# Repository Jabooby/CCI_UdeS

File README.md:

# CCI_UdeS
Concours de Circuit Imprimé Université de Sherbrooke
## Compétition de Conception de PCB - Hacker Mouse

Bienvenue à la compétition de conception de PCB sur le thème "Hacker Mouse" ! Cette compétition vise à stimuler la créativité et l'innovation dans la conception de circuits imprimés pour créer une souris d'ordinateur unique et fonctionnelle.

### Compétition

#### Répertoire "Competition"
Le répertoire "Competition" contient tous les documents nécessaires pour participer à la compétition Hacker Mouse. Vous y trouverez :
- Les règles de la compétition
- Les critères de notation
- Les dates importantes
- Les détails sur les inscriptions
- Autres ressources utiles

#### Répertoires des Équipes
Chaque équipe participant à la compétition aura son propre répertoire dédié dans lequel elle pourra stocker ses fichiers de conception, ses notes, ses schémas, ses designs de PCB et toute autre documentation pertinente liée à son projet.

### Documentation

#### Répertoire "Documentation"
Le répertoire "Documentation" contient des fichiers PDF de datasheets des microcontrôleurs acceptés pour la compétition. Ces documents sont essentiels pour comprendre les spécifications techniques des composants utilisés dans la conception des "Hacker Mouse".

### Ressources Supplémentaires

- Si vous avez des questions ou avez besoin d'aide, n'hésitez pas à nous contacter.
- Rejoignez notre canal Discord pour discuter avec d'autres participants et obtenir des conseils et des astuces.

Nous vous souhaitons bonne chance et avons hâte de voir vos créations !

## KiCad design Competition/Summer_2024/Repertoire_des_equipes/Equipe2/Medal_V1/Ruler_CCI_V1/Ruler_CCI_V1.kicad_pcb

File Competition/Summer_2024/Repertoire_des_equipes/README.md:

# Création de "Branch"

 1. Cliquez sur le rectangle avec le logo de "Branche". 
 2. Puis cliquez sur "View all branches".

 3. Dans la nouvelle fenêtre, cliquez sur "New branch".

 4. Choisissez un nom de "Branch" et appuyez sur "Create new branch".

 5. Votre "Branch" est maitenant créé. Vous pouvez ouvrir "GitHub Desktop" ou "GitKraken" et sélectionner la "Branch" que vous voulez.

 6. Bon codage!

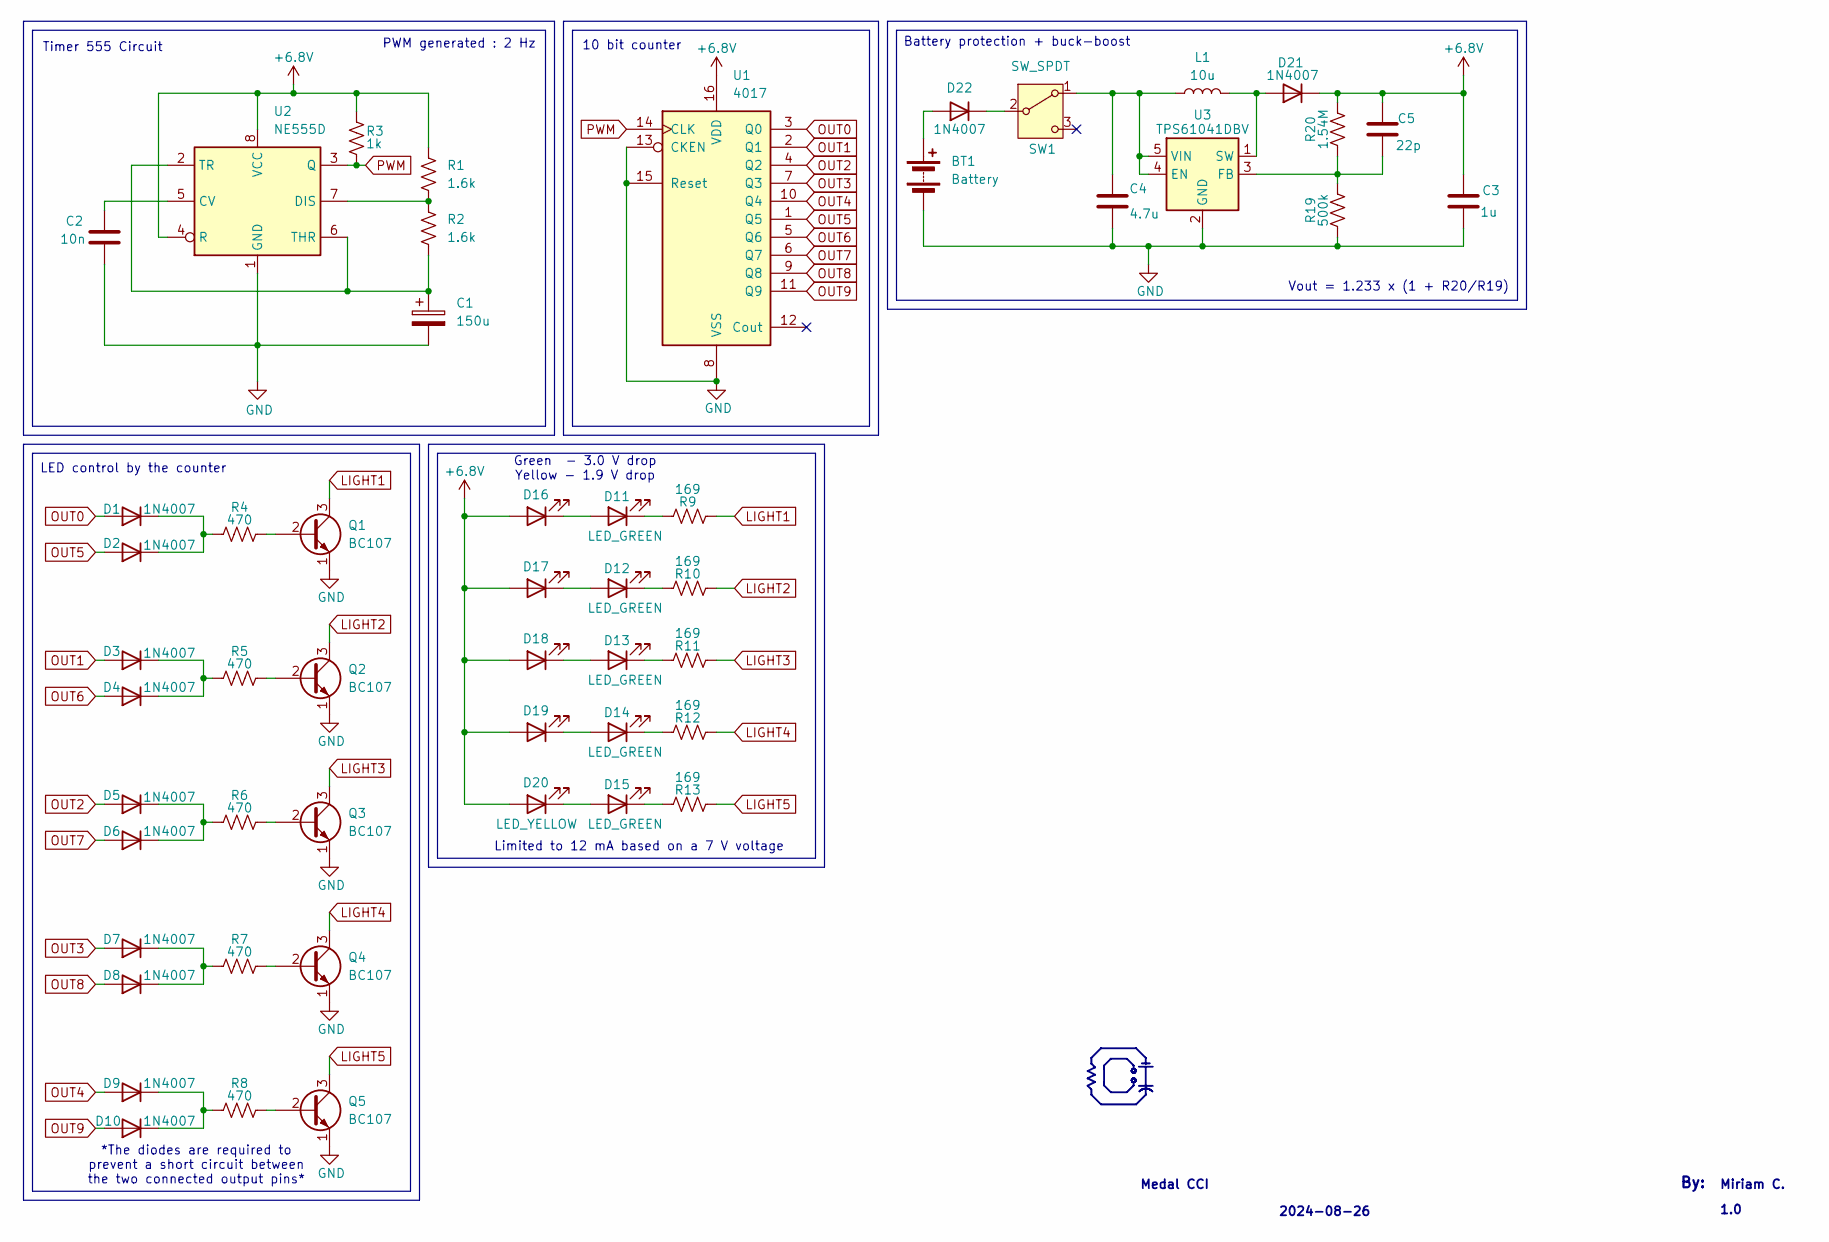
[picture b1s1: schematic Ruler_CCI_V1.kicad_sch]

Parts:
BT1: Battery; BAT_SMD_CR1220
C1: 150u; CP_Elec_6.3x7.7
C2: 10n; C_0603_1608Metric
C3: 1u; L_0603_1608Metric_Pad1.05x0.95mm_HandSolder
C4: 4.7u; L_0603_1608Metric_Pad1.05x0.95mm_HandSolder
C5: 22p; L_0603_1608Metric_Pad1.05x0.95mm_HandSolder
D1, D2, D3, D4, D5, D6, D7, D8, D9, D10, D21, D22: 1N4007; D_SOD-123F
D11, D12, D13, D14, D15: LED_GREEN; D_0603_1608Metric_Pad1.05x0.95mm_HandSolder
D16, D17, D18, D19, D20: LED_YELLOW; D_0603_1608Metric_Pad1.05x0.95mm_HandSolder
L1: 10u; L_0805_2012Metric_Pad1.15x1.40mm_HandSolder
Q1, Q2, Q3, Q4, Q5: BC107; SOT-23
R1, R2: 1.6k; R_0603_1608Metric_Pad0.98x0.95mm_HandSolder
R3: 1k; R_0603_1608Metric_Pad0.98x0.95mm_HandSolder
R4, R5, R6, R7, R8: 470; R_0603_1608Metric_Pad0.98x0.95mm_HandSolder
R9, R10, R11, R12, R13: 169; R_0603_1608Metric_Pad0.98x0.95mm_HandSolder
R19: 500k; R_0603_1608Metric_Pad0.98x0.95mm_HandSolder
R20: 1.54M; R_0603_1608Metric_Pad0.98x0.95mm_HandSolder
SW1: SW_SPDT; SW_SPDT_PCM12
U1: 4017; SOP-16_3.9x9.9mm_P1.27mm
U2: NE555D; SOIC-8_3.9x4.9mm_P1.27mm
U3: TPS61041DBV; SOT-23-5

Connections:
+6.8V: C3.1, C5.1, D16.2 (A), D17.2 (A), D18.2 (A), D19.2 (A), D20.2 (A), D21.1 (K), R1.1, R3.1, R20.2, U1.16 (VDD), U2.4 (R), U2.8 (VCC)
GND: BT1.2 (-), C1.2, C2.2, C3.2, C4.2, Q1.1 (E), Q2.1 (E), Q3.1 (E), Q4.1 (E), Q5.1 (E), R19.1, U1.8 (VSS), U1.13 (CKEN), U1.15 (Reset), U2.1 (GND), U3.2 (GND)
LIGHT1: Q1.3 (C), R9.1
LIGHT2: Q2.3 (C), R10.1
LIGHT3: Q3.3 (C), R11.1
LIGHT4: Q4.3 (C), R12.1
LIGHT5: Q5.3 (C), R13.1
unnamed: BT1.1 (+), D22.2 (A)
unnamed: D1.1 (K), D2.1 (K), R4.1
unnamed: D3.1 (K), D4.1 (K), R5.1
unnamed: D5.1 (K), D6.1 (K), R6.1
unnamed: D7.1 (K), D8.1 (K), R7.1
unnamed: D9.1 (K), D10.1 (K), R8.1
unnamed: D11.2 (A), D16.1 (K)
unnamed: D11.1 (K), R9.2
unnamed: D12.2 (A), D17.1 (K)
unnamed: D12.1 (K), R10.2
unnamed: D13.2 (A), D18.1 (K)
unnamed: D13.1 (K), R11.2
unnamed: D14.2 (A), D19.1 (K)
unnamed: D14.1 (K), R12.2
unnamed: D15.2 (A), D20.1 (K)
unnamed: D15.1 (K), R13.2
unnamed: D21.2 (A), L1.2, U3.1 (SW)
unnamed: D22.1 (K), SW1.2 (B)
unnamed: Q1.2 (B), R4.2
unnamed: Q2.2 (B), R5.2
unnamed: Q3.2 (B), R6.2
unnamed: Q4.2 (B), R7.2
unnamed: Q5.2 (B), R8.2
unnamed: C4.1, L1.1, SW1.1 (A), U3.4 (EN), U3.5 (VIN)
unnamed: C2.1, U2.5 (CV)
unnamed: R1.2, R2.1, U2.7 (DIS)
unnamed: C1.1, R2.2, U2.2 (TR), U2.6 (THR)
unnamed: C5.2, R19.2, R20.1, U3.3 (FB)
OUT0: D1.2 (A), U1.3 (Q0)
OUT1: D3.2 (A), U1.2 (Q1)
OUT2: D5.2 (A), U1.4 (Q2)
OUT3: D7.2 (A), U1.7 (Q3)
OUT4: D9.2 (A), U1.10 (Q4)
OUT5: D2.2 (A), U1.1 (Q5)
OUT6: D4.2 (A), U1.5 (Q6)
OUT7: D6.2 (A), U1.6 (Q7)
OUT8: D8.2 (A), U1.9 (Q8)
OUT9: D10.2 (A), U1.11 (Q9)
PWM: R3.2, U1.14 (CLK), U2.3 (Q)

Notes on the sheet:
Miriam C.
10 bit counter
2024-08-26
Limited to 12 mA based on a 7 V voltage
LED control by the counter
Green - 3.0 V drop Yellow - 1.9 V drop
By:
1.0
Battery protection + buck-boost
PWM generated : 2 Hz
Timer 555 Circuit
*The diodes are required to prevent a short circuit between the two connected output pins*
Vout = 1.233 x (1 + R20/R19)
Medal CCI

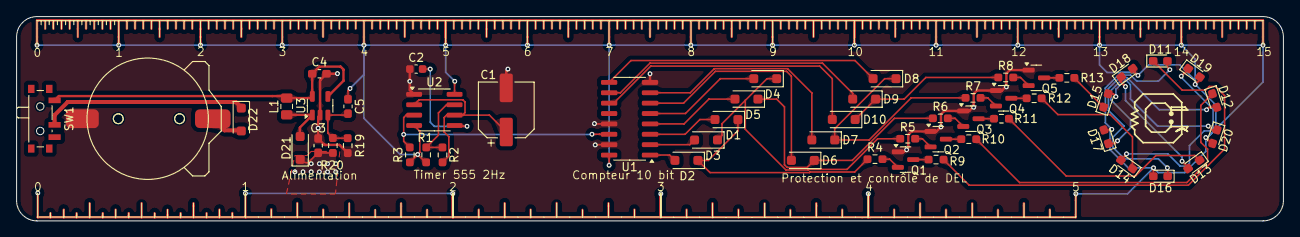
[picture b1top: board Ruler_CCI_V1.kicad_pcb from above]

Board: 2 copper layers, 155.0 x 25.0 mm, 53 parts (0 on the bottom side), 46 nets.

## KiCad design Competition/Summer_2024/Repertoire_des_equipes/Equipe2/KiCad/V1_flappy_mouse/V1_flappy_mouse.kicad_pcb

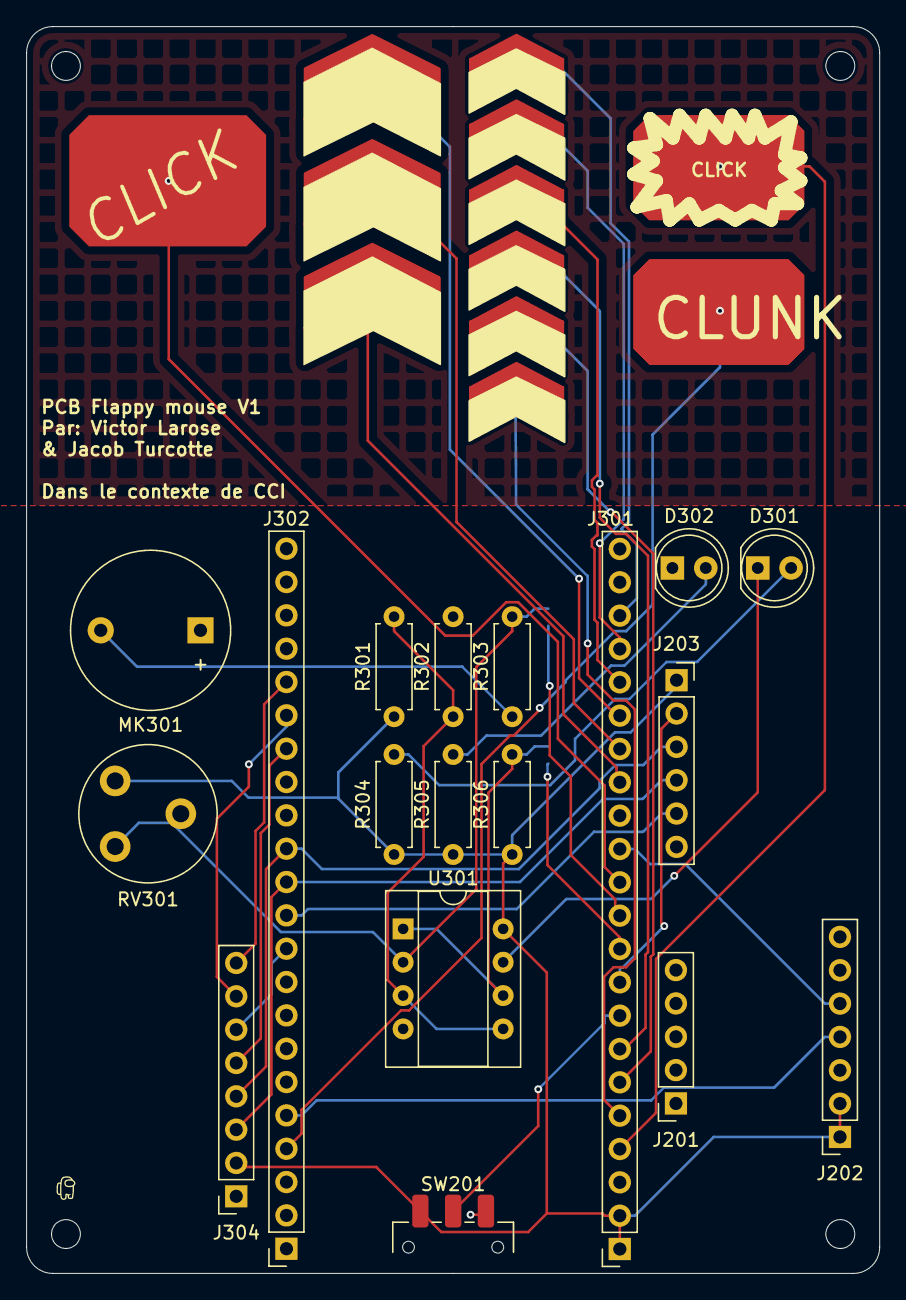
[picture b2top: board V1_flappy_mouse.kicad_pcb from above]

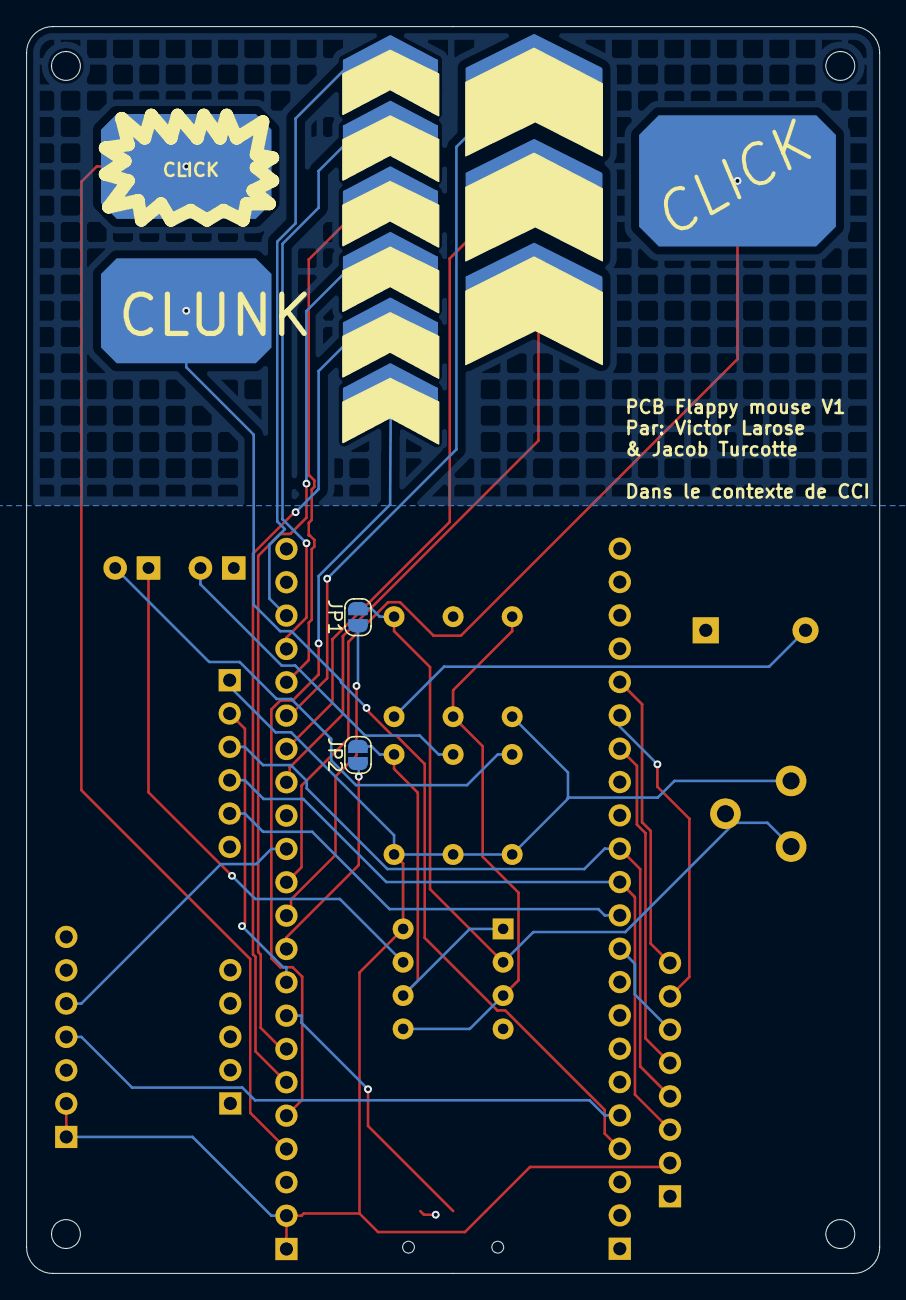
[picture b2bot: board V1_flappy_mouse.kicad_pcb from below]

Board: 4 copper layers, 65.0 x 95.0 mm, 43 parts (14 on the bottom side), 34 nets.

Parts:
D301: TRIG LED; LED_D5.0mm_IRGrey
D302: PWR LED; LED_D5.0mm_IRGrey
J201: Conn_01x05_no_connect(SPI); PinSocket_1x05_P2.54mm_Vertical
J202: Conn_accelerometer_I2C; PinSocket_1x07_P2.54mm_Vertical
J203: Conn_Module_SD; PinSocket_1x06_P2.54mm_Vertical
J301: ESP_GAUCHE; PinSocket_1x22_P2.54mm_Vertical
J302: ESP_DROIT; PinSocket_1x22_P2.54mm_Vertical
J304: Conn_TFT_display; PinSocket_1x08_P2.54mm_Vertical
JP1: SolderJumper_AOUT; SolderJumper-2_P1.3mm_Open_RoundedPad1.0x1.5mm
JP2: SolderJumper_DOUT; SolderJumper-2_P1.3mm_Open_RoundedPad1.0x1.5mm
MK301: Mic; Buzzer_12x9.5RM7.6
R301, R302: 100K; R_Axial_DIN0207_L6.3mm_D2.5mm_P7.62mm_Horizontal
R303: 150; R_Axial_DIN0207_L6.3mm_D2.5mm_P7.62mm_Horizontal
R304, R305: 1K; R_Axial_DIN0207_L6.3mm_D2.5mm_P7.62mm_Horizontal
R306: 10K; R_Axial_DIN0207_L6.3mm_D2.5mm_P7.62mm_Horizontal
RV301: 10K; Potentiometer_Piher_PT-10-V05_Vertical
SW201: JS102011JAQN; SW_SPDT_CK_JS102011SAQN
TP5, TP5#2: Touchpad_click_gauche; Touchpad_biz_rect_smaller
TP6, TP6#2: Touchpad_scroll4; Touchpad_slider_smaller
TP7, TP7#2: Touchpad_scroll5; Touchpad_slider_smaller
TP8, TP8#2: Touchpad_scroll6; Touchpad_slider_smaller
TP9, TP9#2: Touchpad_scroll7; Touchpad_slider_smaller
TP10, TP10#2: Touchpad_scroll8; Touchpad_slider_smaller
TP11, TP11#2: Touchpad_scroll9; Touchpad_slider_smaller
TP12, TP12#2: Touchpad_stopMouseMotion; Touchpad_biz_rect_smaller
TP201: Touchpad_click_droit; Touchpad_biz_rect
TP202, TP202#2: Touchpad_scroll1; Touchpad_slider
TP203, TP203#2: Touchpad_scroll2; Touchpad_slider
TP204, TP204#2: Touchpad_scroll3; Touchpad_slider
U301: LM393; CERDIP-8_W7.62mm_SideBrazed_Socket

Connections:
+3.3V: J202.1, J202.2, J203.1, J301.1, J301.2, J304.2, R301.1, R304.1, R305.1, R306.1, RV301.3, SW201.1 (A), U301.8 (V+)
FSPICLK/TOUCH12/GPIO12: J301.18, TP9.1, TP9#2.1
FSPICS0/TOUCH10/GPIO10: J301.16, TP203.1, TP203#2.1
FSPID/TOUCH11/GPIO11: J301.17, TP204.1, TP204#2.1
FSPIHD/TOUCH9/GPIO9: J301.15, TP202.1, TP202#2.1
FSPIQ/TOUCH13/GPIO13: J301.19, TP10.1, TP10#2.1
FSPIWP/TOUCH14/GPIO14: J301.20, TP11.1, TP11#2.1
GND: D302.1 (K), J202.3, J202.7, J203.6, J301.22, J302.1, J302.21, J302.22, J304.1, MK301.1 (-), R302.2, SW201.3 (C), U301.4 (V-)
GPIO1/TOUCH1/ADC1_0/SDA0: J302.4, TP12.1, TP12#2.1
GPIO2/TOUCH2/ADC1_1/SCL1: J202.4, J302.5
GPIO21: J302.18, J304.8
GPIO35/FSPID: J203.3, J302.13, J304.4
GPIO36/FSPICLK: J203.4, J302.12, J304.3
GPIO37/FSPIQ: J203.5, J302.11
GPIO38/FSPIWP/RGB_LED: J302.10, J304.6
GPIO47/SPICLK_P: J302.17, J304.7
GPIO48/SPICLK_N: J302.16, J304.5
JTAG/TOUCH3/SDA1/GPIO3: J202.5, J301.13
unnamed: D301.2 (A), R304.2
unnamed: D301.1 (K), U301.7
unnamed: D302.2 (A), R305.2
unnamed: JP1.1 (A), R303.2, RV301.1, RV301.2, U301.2 (-)
unnamed: JP2.1 (A), R306.2, U301.1, U301.6 (-)
unnamed: MK301.2 (+), R303.1
unnamed: R301.2, R302.1, U301.3 (+), U301.5 (+)
TOUCH4/GPIO4: J301.4, TP5.1, TP5#2.1
TOUCH5/GPIO5: J301.5, TP6.1, TP6#2.1
TOUCH6/GPIO6: J301.6, TP7.1, TP7#2.1
TOUCH7/GPIO7: J301.7, TP8.1, TP8#2.1
TOUCH8/GPIO8: J301.12, TP201.1
U0CTS/GPIO16: J203.2, J301.9
U0RTS/GPIO15: J301.8, SW201.2 (B)
U1RXD/GPIO18: J301.11, JP1.2 (B)
U1TXD/GPIO17: J301.10, JP2.2 (B)

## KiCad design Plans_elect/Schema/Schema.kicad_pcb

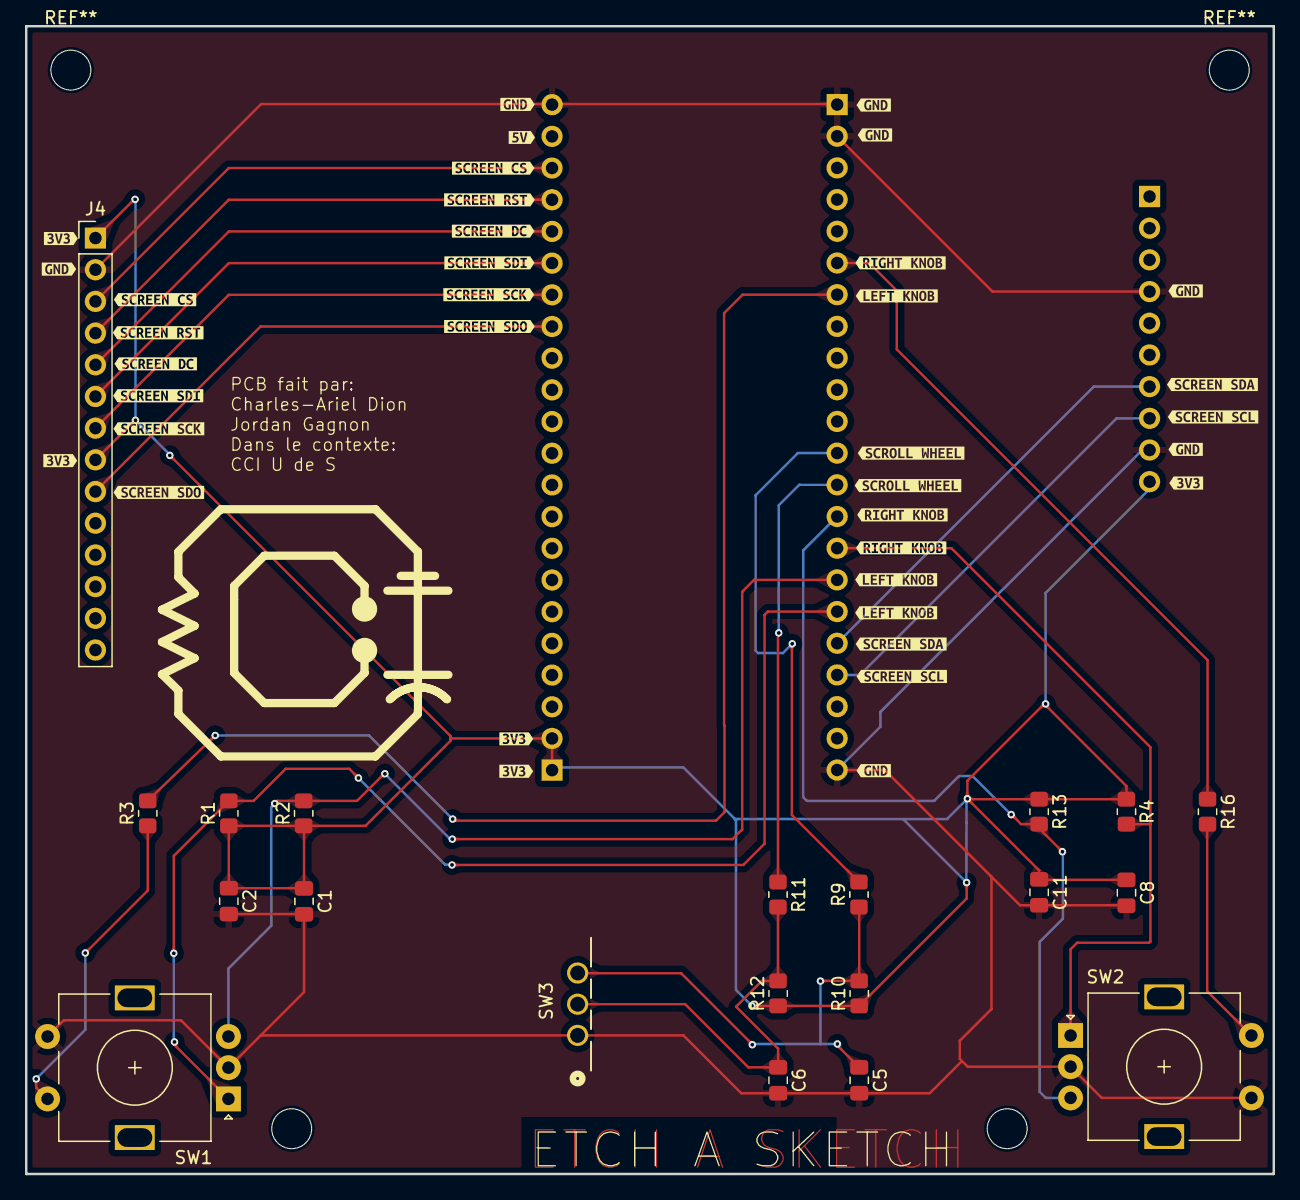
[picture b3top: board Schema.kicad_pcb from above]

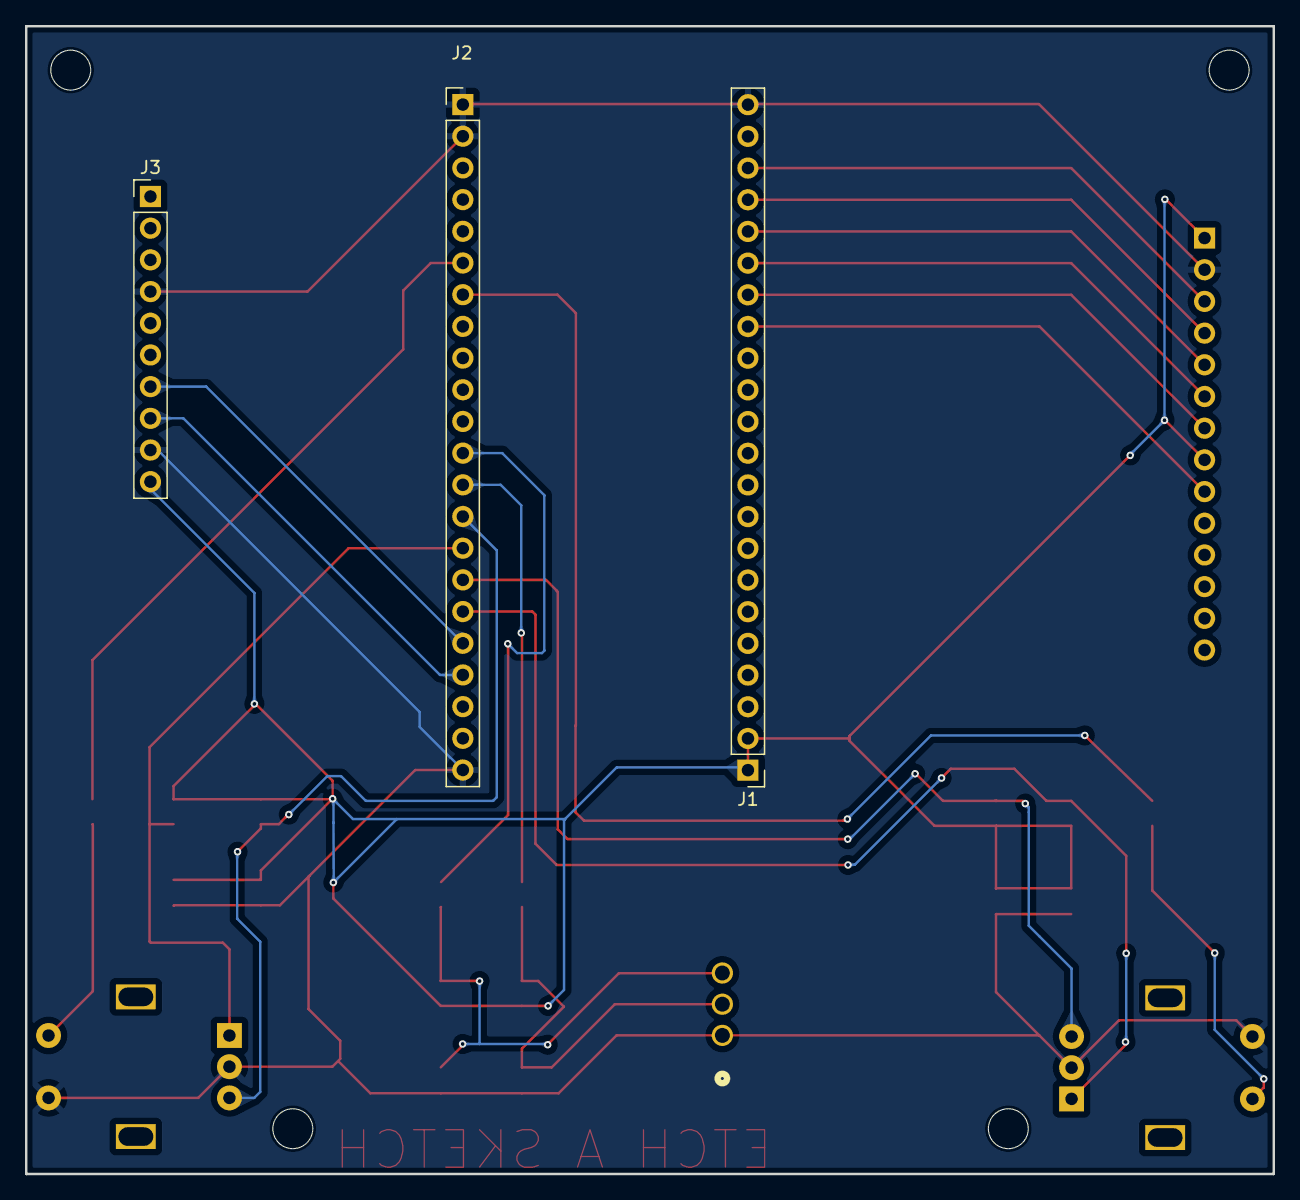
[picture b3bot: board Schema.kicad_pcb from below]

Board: 2 copper layers, 100.0 x 92.0 mm, 60 parts (3 on the bottom side), 22 nets.

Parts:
C1, C2, C8, C11: 100nF; C_0805_2012Metric_Pad1.18x1.45mm_HandSolder
C5, C6: 22nF; C_0805_2012Metric_Pad1.18x1.45mm_HandSolder
J1, J2: Conn_01x22; PinHeader_1x22_P2.54mm_Vertical
J3: Conn_01x10; PinHeader_1x10_P2.54mm_Vertical
J4: Conn_01x14; PinHeader_1x14_P2.54mm_Vertical
R1, R2, R3, R4, R13, R16: 1K; R_0805_2012Metric_Pad1.20x1.40mm_HandSolder
R9, R10, R11, R12: 10K; R_0805_2012Metric_Pad1.20x1.40mm_HandSolder
SW1, SW2: RotaryEncoder_Switch; RotaryEncoder_Alps_EC11E-Switch_Vertical_H20mm
SW3: RotaryEncoder; EN10HT_BIT
kibuzzard-66ACC1A1: G***; kibuzzard-66ACC1A1
kibuzzard-66ACC1C4: G***; kibuzzard-66ACC1C4
kibuzzard-66ACC1D0: G***; kibuzzard-66ACC1D0
kibuzzard-66ACC1F2: G***; kibuzzard-66ACC1F2
kibuzzard-66ACC2A7, kibuzzard-66ACC2A7#2, kibuzzard-66ACC2A7#3: G***; kibuzzard-66ACC2A7
kibuzzard-66ACC2DC, kibuzzard-66ACC2DC#2, kibuzzard-66ACC2DC#3: G***; kibuzzard-66ACC2DC
kibuzzard-66ACC3A5, kibuzzard-66ACC3A5#2: G***; kibuzzard-66ACC3A5
kibuzzard-66ACC4A4: G***; kibuzzard-66ACC4A4
kibuzzard-66ACC4E0: G***; kibuzzard-66ACC4E0
kibuzzard-66ACC21E: G***; kibuzzard-66ACC21E
kibuzzard-66ACC22A: G***; kibuzzard-66ACC22A
kibuzzard-66ACC25D, kibuzzard-66ACC25D#2, kibuzzard-66ACC25D#3, kibuzzard-66ACC25D#4: G***; kibuzzard-66ACC25D
kibuzzard-66ACC45C: G***; kibuzzard-66ACC45C
kibuzzard-66ACC46C: G***; kibuzzard-66ACC46C
kibuzzard-66ACC47C: G***; kibuzzard-66ACC47C
kibuzzard-66ACC49B: G***; kibuzzard-66ACC49B
kibuzzard-66ACC153, kibuzzard-66ACC153#2: G***; kibuzzard-66ACC153
kibuzzard-66ACC180, kibuzzard-66ACC180#2, kibuzzard-66ACC180#3, kibuzzard-66ACC180#4: G***; kibuzzard-66ACC180
kibuzzard-66ACC204: G***; kibuzzard-66ACC204
kibuzzard-66ACC281: G***; kibuzzard-66ACC281
kibuzzard-66ACC309, kibuzzard-66ACC309#2: G***; kibuzzard-66ACC309
kibuzzard-66ACC392, kibuzzard-66ACC392#2: G***; kibuzzard-66ACC392
kibuzzard-66ACC438: G***; kibuzzard-66ACC438

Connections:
3V3: C1.1, C2.1, C8.1, C11.1, J1.1, J1.2, J3.10, J4.1, J4.8, R1.1, R2.1, R4.1, R10.1, R12.1, R13.1
/GPIO1-SCL: J2.19, J3.8
/GPIO2-SDA: J2.18, J3.7
/GPIO9-SDO: J1.15, J4.9
/GPIO10-SCk: J1.16, J4.7
/GPIO11-SDI: J1.17, J4.6
/GPIO12-DC: J1.18, J4.5
/GPIO13-RESET: J1.19, J4.4
/GPIO14-CS: J1.20, J4.3
/GPIO37-chB_S: J2.12, R9.2
/GPIO38_chA_S: J2.13, R11.1
/GPIO39-chB_Y: J2.14, R13.2, SW2.B
/GPIO40-chA_Y: J2.15, R4.2, SW2.A
/GPIO41-chB_X: J2.16, R2.2, SW1.B
/GPIO42-chA_X: J2.17, R1.2, SW1.A
/GPIO47-BSW2: J2.6, R16.1
/GPIO48-BSW1: J2.7, R3.2
GND: C1.2, C2.2, C5.2, C6.2, C8.2, C11.2, J1.22, J2.1, J2.2, J2.22, J3.4, J3.9, J4.2, SW1.C, SW1.S1, SW2.C, SW2.S1
unnamed: C5.1, R9.1, R10.2
unnamed: C6.1, R11.2, R12.2
unnamed: R3.1, SW1.S2
unnamed: R16.2, SW2.S2

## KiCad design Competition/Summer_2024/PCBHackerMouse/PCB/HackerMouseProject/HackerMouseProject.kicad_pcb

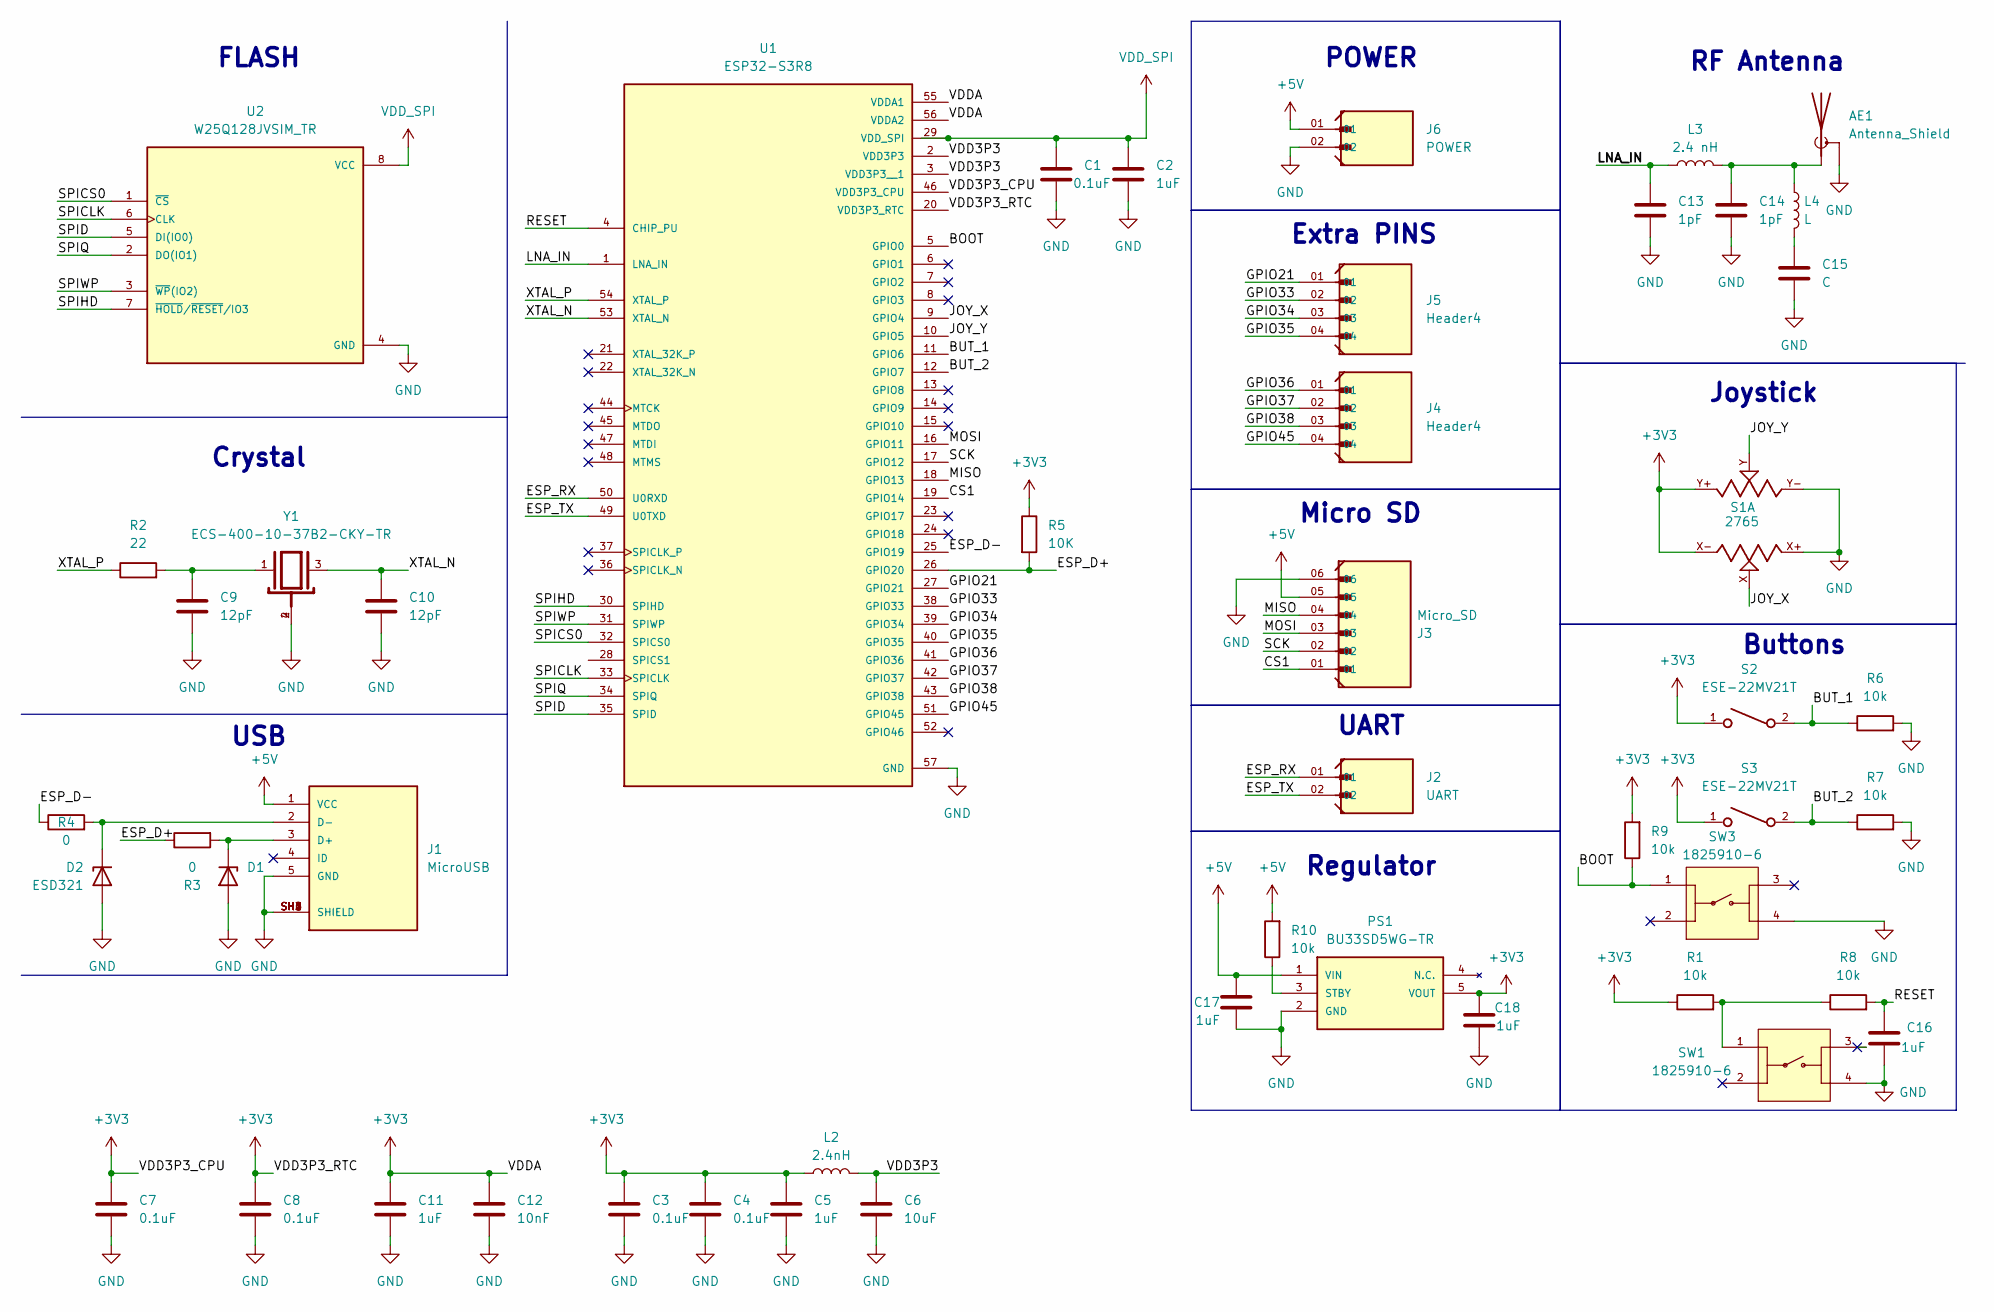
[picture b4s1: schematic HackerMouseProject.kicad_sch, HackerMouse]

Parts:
AE1: Antenna_Shield
C1, C3, C4, C7, C8: 0.1uF; C_0603_1608Metric_Pad1.08x0.95mm_HandSolder
C2, C5, C11, C16, C17, C18: 1uF; C_0603_1608Metric_Pad1.08x0.95mm_HandSolder
C6: 10uF; C_0603_1608Metric_Pad1.08x0.95mm_HandSolder
C9, C10: 12pF; C_0603_1608Metric_Pad1.08x0.95mm_HandSolder
C12: 10nF; C_0603_1608Metric_Pad1.08x0.95mm_HandSolder
C13, C14: 1pF; C_0603_1608Metric_Pad1.08x0.95mm_HandSolder
C15: C; C_0603_1608Metric_Pad1.08x0.95mm_HandSolder
D1, D2: ESD321; D_SOD-523
J1: MicroUSB; AMPHENOL_10118194-0001LF; PARTREV D
J2: UART; WURTH_61300211121; PARTREV 07/31/2015
J3: Micro_SD; WURTH_61300611121
J4, J5: Header4; WURTH_61300411121
J6: POWER; WURTH_61300211121; PARTREV 07/31/2015
L2: 2.4nH; C_0603_1608Metric_Pad1.08x0.95mm_HandSolder
L3: 2.4 nH; C_0603_1608Metric_Pad1.08x0.95mm_HandSolder
L4: L; C_0603_1608Metric_Pad1.08x0.95mm_HandSolder
PS1: BU33SD5WG-TR; SOT95P280X125-5N; MOUSER_PART_NUMBER 755-BU33SD5WG-TR
R1, R6, R7, R8, R9, R10: 10k; R_0603_1608Metric_Pad0.98x0.95mm_HandSolder
R2: 22; R_0603_1608Metric_Pad0.98x0.95mm_HandSolder
R3, R4: 0; R_0603_1608Metric_Pad0.98x0.95mm_HandSolder
R5: 10K; R_0603_1608Metric_Pad0.98x0.95mm_HandSolder
S1: 2765
S2, S3: ESE-22MV21T; SW_ESE-22MV21T
SW1, SW3: 1825910-6; SW_1825910-6-4; PARTREV C10
U1: ESP32-S3R8; QFN40P700X700X90-57N
U2: W25Q128JVSIM_TR; PARTREV C
Y1: ECS-400-10-37B2-CKY-TR; XTAL_ECS-400-10-37B2-CKY-TR; PARTREV Rev.2021

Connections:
+3V3: C3.1, C4.1, C5.1, C7.1, C8.1, C11.1, C12.1, C18.1, L2.2, PS1.5 (VOUT), R1.1, R5.1, R9.2, S1.X-, S1.Y+, S2.1, S3.1, U1.20 (VDD3P3_RTC), U1.46 (VDD3P3_CPU), U1.55 (VDDA1), U1.56 (VDDA2)
+5V: C17.1, J1.1 (VCC), J3.05, J6.01, PS1.1 (VIN), R10.2
/BOOT: R9.1, SW3.1, U1.5 (GPIO0)
/BUT_1: R6.1, S2.2, U1.11 (GPIO6)
/BUT_2: R7.1, S3.2, U1.12 (GPIO7)
/CS1: J3.01, U1.19 (GPIO14)
/ESP_D+: R3.1, R5.2, U1.26 (GPIO20)
/ESP_D-: R4.1, U1.25 (GPIO19)
/ESP_RX: J2.01, U1.50 (U0RXD)
/ESP_TX: J2.02, U1.49 (U0TXD)
/GPIO21: J5.01, U1.27 (GPIO21)
/GPIO33: J5.02, U1.38 (GPIO33)
/GPIO34: J5.03, U1.39 (GPIO34)
/GPIO35: J5.04, U1.40 (GPIO35)
/GPIO36: J4.01, U1.41 (GPIO36)
/GPIO37: J4.02, U1.42 (GPIO37)
/GPIO38: J4.03, U1.43 (GPIO38)
/GPIO45: J4.04, U1.51 (GPIO45)
/JOY_X: S1.X, U1.9 (GPIO4)
/JOY_Y: S1.Y, U1.10 (GPIO5)
/LNA_IN: C13.1, L3.1, U1.1 (LNA_IN)
/MISO: J3.04, U1.18 (GPIO13)
/MOSI: J3.03, U1.16 (GPIO11)
/RESET: C16.1, R8.2, U1.4 (CHIP_PU)
/SCK: J3.02, U1.17 (GPIO12)
/SPICLK: U1.33 (SPICLK), U2.6 (CLK)
/SPICS0: U1.32 (SPICS0), U2.1 (~CS)
/SPID: U1.35 (SPID), U2.5 (DI(IO0))
/SPIHD: U1.30 (SPIHD), U2.7 (~HOLD/~RESET/IO3)
/SPIQ: U1.34 (SPIQ), U2.2 (DO(IO1))
/SPIWP: U1.31 (SPIWP), U2.3 (~WP(IO2))
/VDD3P3: C6.1, L2.1, U1.2 (VDD3P3), U1.3 (VDD3P3__1)
/XTAL_N: C10.1, U1.53 (XTAL_N), Y1.3
/XTAL_P: R2.1, U1.54 (XTAL_P)
GND: AE1.2 (Shield), C1.2, C2.2, C3.2, C4.2, C5.2, C6.2, C7.2, C8.2, C9.2, C10.2, C11.2, C12.2, C13.2, C14.2, C15.2, C16.2, C17.2, C18.2, D1.2 (A), D2.2 (A), J1.5 (GND), J1.SH1 (SHIELD), J1.SH2 (SHIELD), J1.SH3 (SHIELD), J1.SH4 (SHIELD), J1.SH5 (SHIELD), J1.SH6 (SHIELD), J3.06, J6.02, PS1.2 (GND), R6.2, R7.2, S1.X+, S1.Y-, SW1.4, SW3.4, U1.57 (GND), U2.4 (GND), Y1.2, Y1.4
unnamed: AE1.1 (A), C14.1, L3.2, L4.1
unnamed: C9.1, R2.2, Y1.1
unnamed: C15.1, L4.2
unnamed: D1.1 (K), J1.3 (D+), R3.2
unnamed: D2.1 (K), J1.2 (D-), R4.2
unnamed: PS1.3 (STBY), R10.1
unnamed: R1.2, R8.1, SW1.1
VDD_SPI: C1.1, C2.1, U1.29 (VDD_SPI), U2.8 (VCC)

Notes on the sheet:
Extra PINS
RF Antenna
Regulator
USB
Joystick
FLASH
UART
Crystal
Buttons
POWER
Micro SD

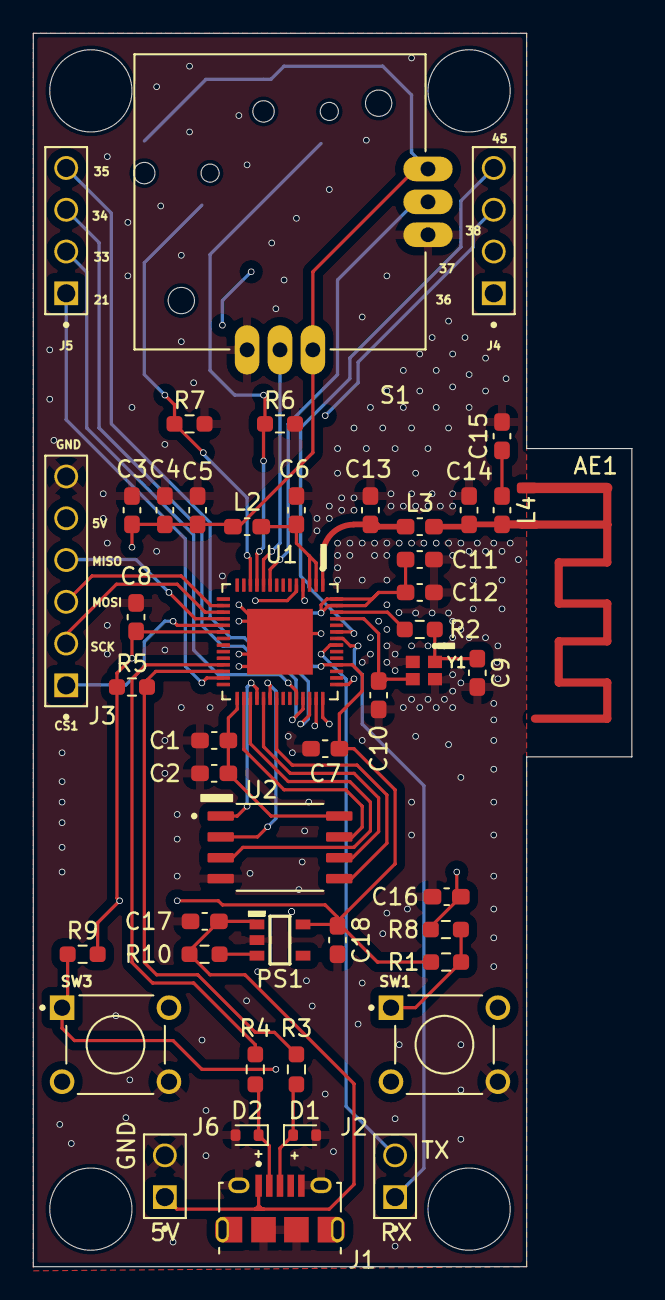
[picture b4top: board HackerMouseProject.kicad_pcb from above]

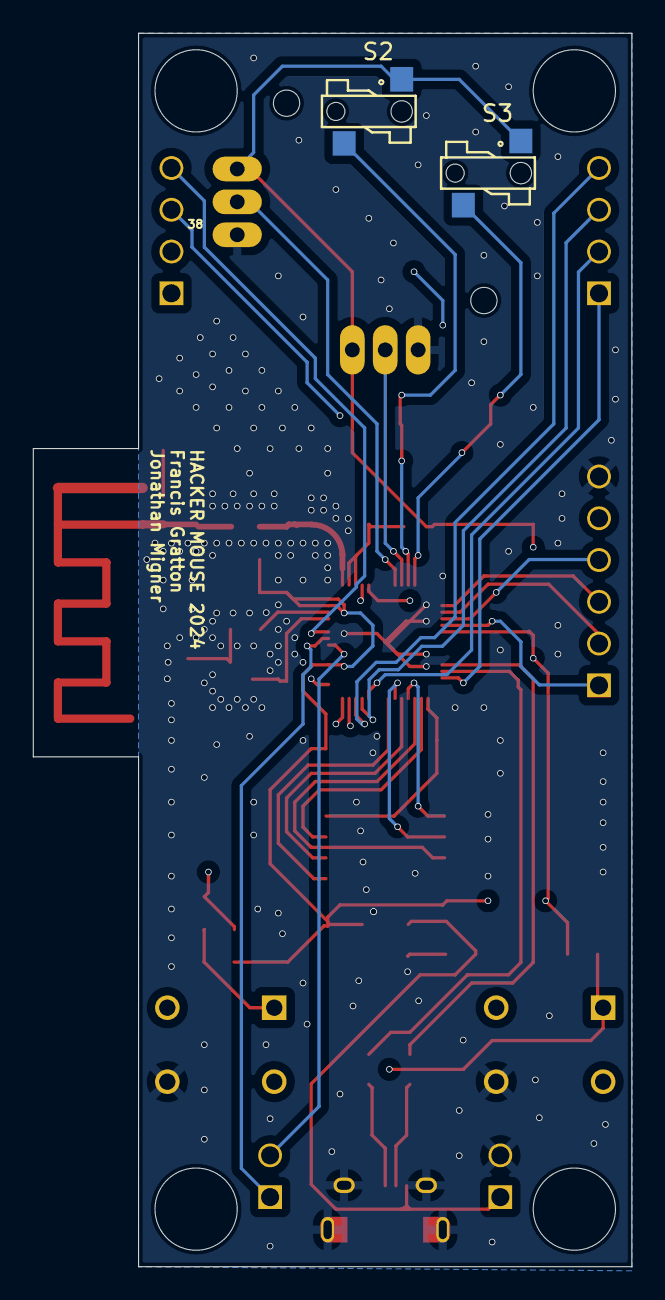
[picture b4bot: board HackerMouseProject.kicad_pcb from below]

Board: 4 copper layers, 36.4 x 75.0 mm, 49 parts (2 on the bottom side), 43 nets.

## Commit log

2024-04-27 1st summit
    hehe
2024-04-27 summit 2
2024-04-27 error fix pdf
2024-04-27 git cheat sheet
2024-04-27 excel participant
2024-04-29 modification du fichier pdf HackerMouse
2024-04-29 excel update
2024-05-11 Création des équipes
2024-05-14 commit de schéma pdf
2024-05-27 push the readme buddy od pal
2024-06-06 Ajout de la présentation Symboles magiques
2024-06-07 Création de notre premier Kicad
2024-06-08 starting the pin out of the ESP32
2024-06-08 completing the pinout (might have to adjust thing)
2024-06-09 apply change for the pinout
2024-06-09 quick push
2024-06-09 quick note of the pinout of the LCD display
2024-06-12 Ajout formulaire d'équipe
2024-06-15 start of the project
2024-06-15 Revert "start of the project"
    This reverts commit 269ee6e23da634a621668b4f64ea07a26a5440e0.
    MB wrong branch
2024-06-20 add pinout of TFT screen and the circuit for the sound sensor
2024-06-20 quick change
2024-06-21 Revert "quick change"
    This reverts commit a655ae3a92829bdf34a6315aef0ea8770937342e.
2024-06-21 change pinout of the LCD
2024-06-22 Push des changements fait
2024-06-22 Push de formulaire à remplir
2024-06-22 Push pcb
2024-06-24 Taking a break, i will come back later today
2024-06-24 formatting and organising code
2024-06-24 adding usb-cdc
2024-06-24 add the component on the PCB
2024-06-25 quick fix
2024-06-25 compositing the usb
2024-06-25 testing new cdcacm config
2024-06-25 tests
2024-06-25 added tasks
2024-06-25 merged
2024-06-25 gitignore moment
2024-06-25 working
2024-06-26 Yes
    Oui
2024-06-26 Buena
2024-06-26 Da
    Formulaire d'idée dument rempli (surely)
2024-06-26 Schematic finished
    The schematic is finished, but some component value needs to be determined
2024-06-26 push pour rien perdre
2024-06-26 Re. Formulaire d'idee
    First time didnt work, we do it again
2024-06-27 First placement of component
2024-06-27 yesyes
    moved my repo, hope it doesnt break everything
2024-06-27 Start Tracing PCB
2024-06-27 Push de PCB compléter à 80%
2024-06-27 pcb 99% terminer
2024-06-27 closed kicad
2024-06-27 PCB without antenna
2024-06-28 all done
2024-06-28 jhvf
2024-07-01 léger changemnt et clarification
2024-07-03 Big vias
2024-07-03 I guess No GND on entenna
2024-07-13 :pencil2: WIP for POC of accelerometer
2024-07-13 Added MPU9250 lib and template project
2024-07-13 tit schéma test Res+Del+Alim
2024-07-13 Plans commencer
2024-07-17 added code start for ch32v203 MCU
2024-07-17 push template
2024-07-18 Added LCD POC
2024-07-22 tit modif
2024-07-27 Encoder works
2024-07-27 PCB
    J'ai un bug ou les footprint ne s'associe pas correctement
2024-07-29 started croquis mec
2024-07-29 plan mec avancer + tit peu delect
2024-07-29 gitgit
2024-07-31 assemblage fait!!!!!!!!!! (c'est trop nice)
    Reste a prendre mesure de hauteur de l'ecran, faire les spacers pis prendre mesure de l'encodeur pour le scroll wheel
2024-07-31 spacer ecran ajouter
2024-08-01 prog updates
2024-08-02 Plan elect finit
    il y a 16 erreurs mais les 16 c'est sur le fait que jai essayer de faire mon propre footprint pis ca fait nimporte quoi
2024-08-02 plans
2024-08-02 FIX ET ADD QUELQUES TRUCS
2024-08-02 push holed
2024-08-02 push gnd et nouveau gerber
2024-08-11 tit changement
2024-08-14 standoff + tol sur boitier
2024-08-15 Mouse, keyboard and storage
2024-08-16 finished for now
2024-08-16 after build
2024-08-16 push code JT
    Code était sur linux avant, tout tranféré vers windows.
    Zip sinon erreur bizarre, merci esp-idf
2024-08-17 Accelero n screen
2024-08-17 PP et 3Dfiles
    Add du powerpoint de presentation et fichiers 3D du case
2024-08-17 Hack Batch files
    Added batch files for hack
2024-08-17 encoders all done
2024-08-17 Works with cmd
2024-08-17 ooko good enough
2024-08-17 All core features done, bonne nuit
2024-08-17 push the code boi
2024-08-17 Update CCI_Presentation_equipe3.pptx
    update powerpoint
2024-08-17 awdasdad
    asdadsa
2024-08-17 Create CCI_2024_[3]_documentation.docx
    Creation docu
2024-08-18 Update Rapport
2024-08-18 should be good
2024-08-18 start the doc
2024-08-18 Docu fini et diagramme
2024-08-18 Update Docu, file name and Schema
2024-08-19 final code and shits
2024-08-19 final code
2024-08-19 final push
2024-08-19 smol update
2024-09-06 PUSH RULER
2024-09-06 push ruler v2
2024-09-06 push panel
